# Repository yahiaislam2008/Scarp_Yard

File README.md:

# Scarp_Yard
A stick for blind people

Simulation:https://wokwi.com/projects/425601854162747393

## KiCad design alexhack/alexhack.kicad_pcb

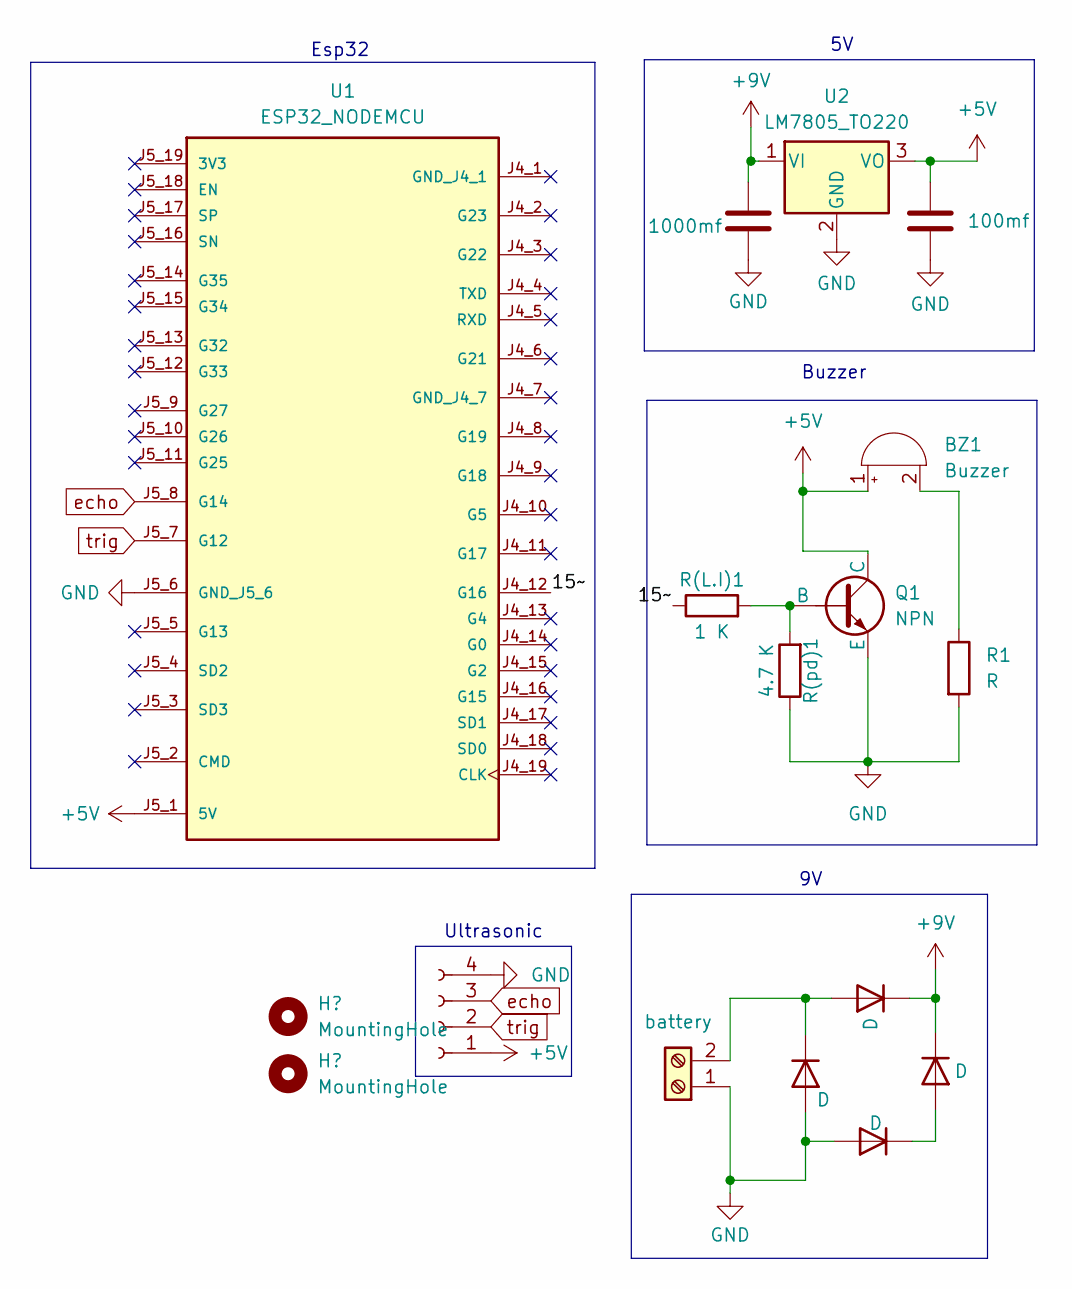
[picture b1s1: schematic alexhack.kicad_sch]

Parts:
BZ1: Buzzer; Buzzer_D14mm_H7mm_P10mm
C1: 1000mf; C_Disc_D3.4mm_W2.1mm_P2.50mm
C2: 100mf; C_Disc_D3.4mm_W2.1mm_P2.50mm
D1, D2, D3, D4: D; D_DO-34_SOD68_P7.62mm_Horizontal
J1: ultra; PinSocket_1x04_P2.54mm_Vertical
J2: battery; TerminalBlock_Phoenix_MKDS-1,5-2-5.08_1x02_P5.08mm_Horizont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
Q1: NPN; JST_B3B-XH-A_LF__SN_
R1: R; R_Axial_DIN0204_L3.6mm_D1.6mm_P5.08mm_Horizontal
R(L.I)1: 1 K; R_Axial_DIN0204_L3.6mm_D1.6mm_P5.08mm_Horizontal
R(pd)1: 4.7 K; R_Axial_DIN0204_L3.6mm_D1.6mm_P5.08mm_Horizontal
U1: ESP32_NODEMCU; MODULE_ESP32_NODEMCU
U2: LM7805_TO220; TO-220-3_Vertical

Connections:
+5V: BZ1.1 (+), C2.1, J1.1, Q1.1 (C), U1.J5_1 (5V), U2.3 (VO)
+9V: C1.1, D2.1 (K), D4.1 (K), U2.1 (VI)
/15~: R(L.I)1.1, U1.J4_12 (G16)
GND: C1.2, C2.2, D1.2 (A), D3.2 (A), J1.4, J2.1, Q1.3 (E), R1.2, R(pd)1.1, U1.J5_6 (GND_J5_6), U2.2 (GND)
unnamed: BZ1.2 (-), R1.1
unnamed: D1.1 (K), D2.2 (A), J2.2
unnamed: D3.1 (K), D4.2 (A)
unnamed: Q1.2 (B), R(L.I)1.2, R(pd)1.2
echo: J1.3, U1.J5_8 (G14)
trig: J1.2, U1.J5_7 (G12)

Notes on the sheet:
Ultrasonic
Buzzer
Esp32

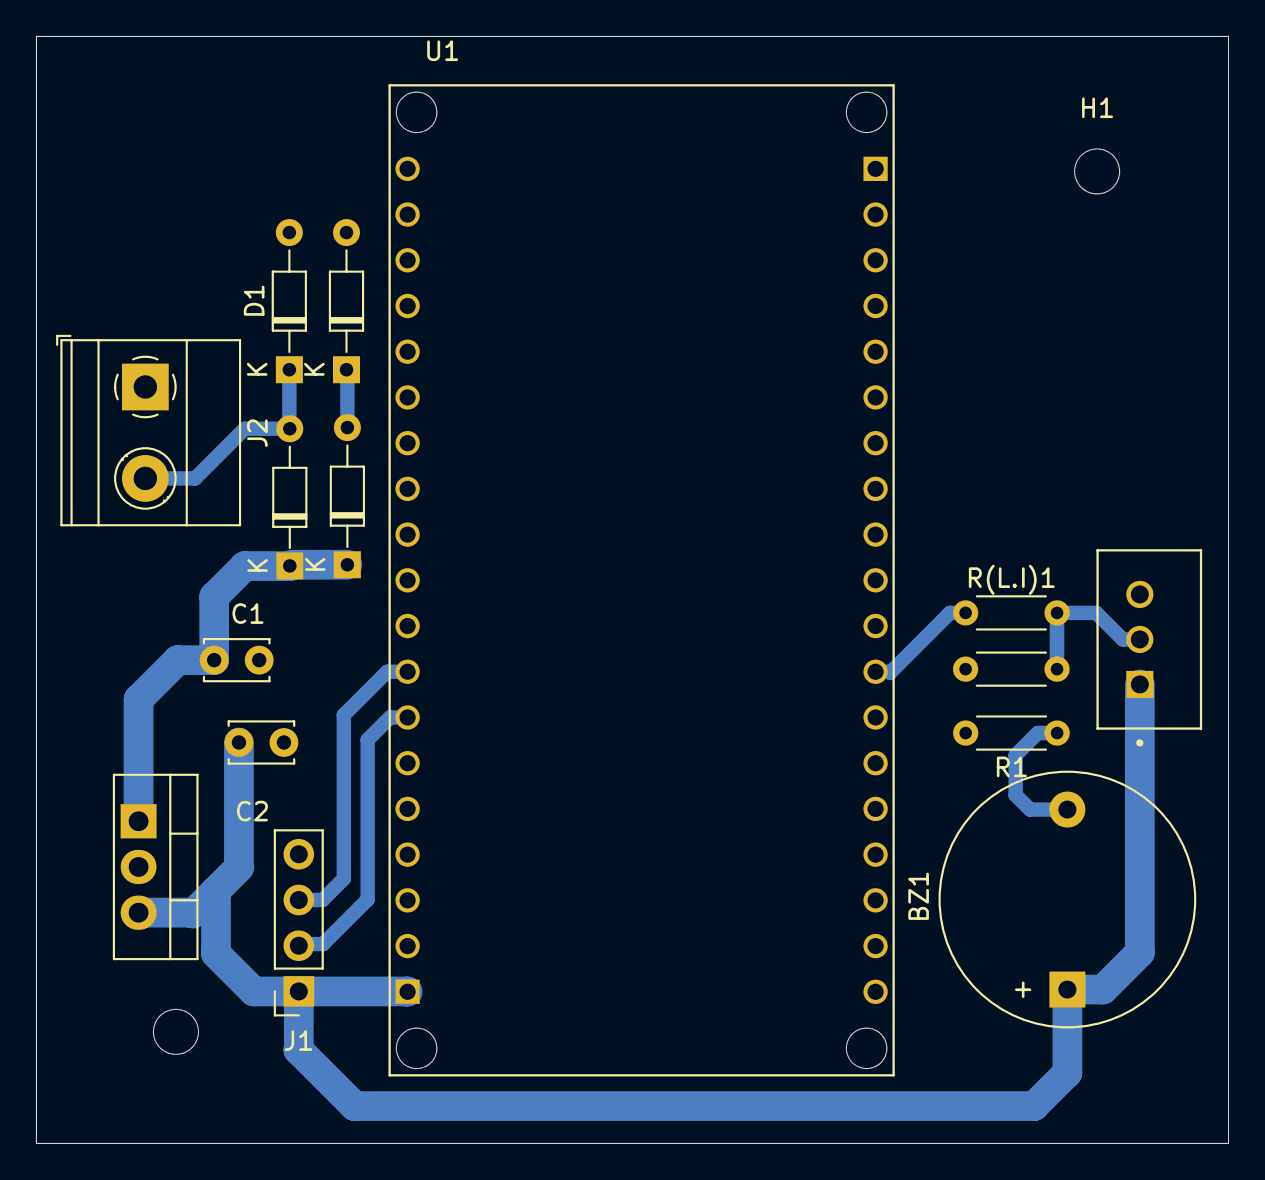
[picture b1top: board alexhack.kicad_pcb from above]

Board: 2 copper layers, 66.2 x 61.5 mm, 17 parts (0 on the bottom side), 10 nets.

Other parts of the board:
H1, H2: MountingHole; MountingHole_2.5mm

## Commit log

2025-03-16 first
2025-03-16 Demo
